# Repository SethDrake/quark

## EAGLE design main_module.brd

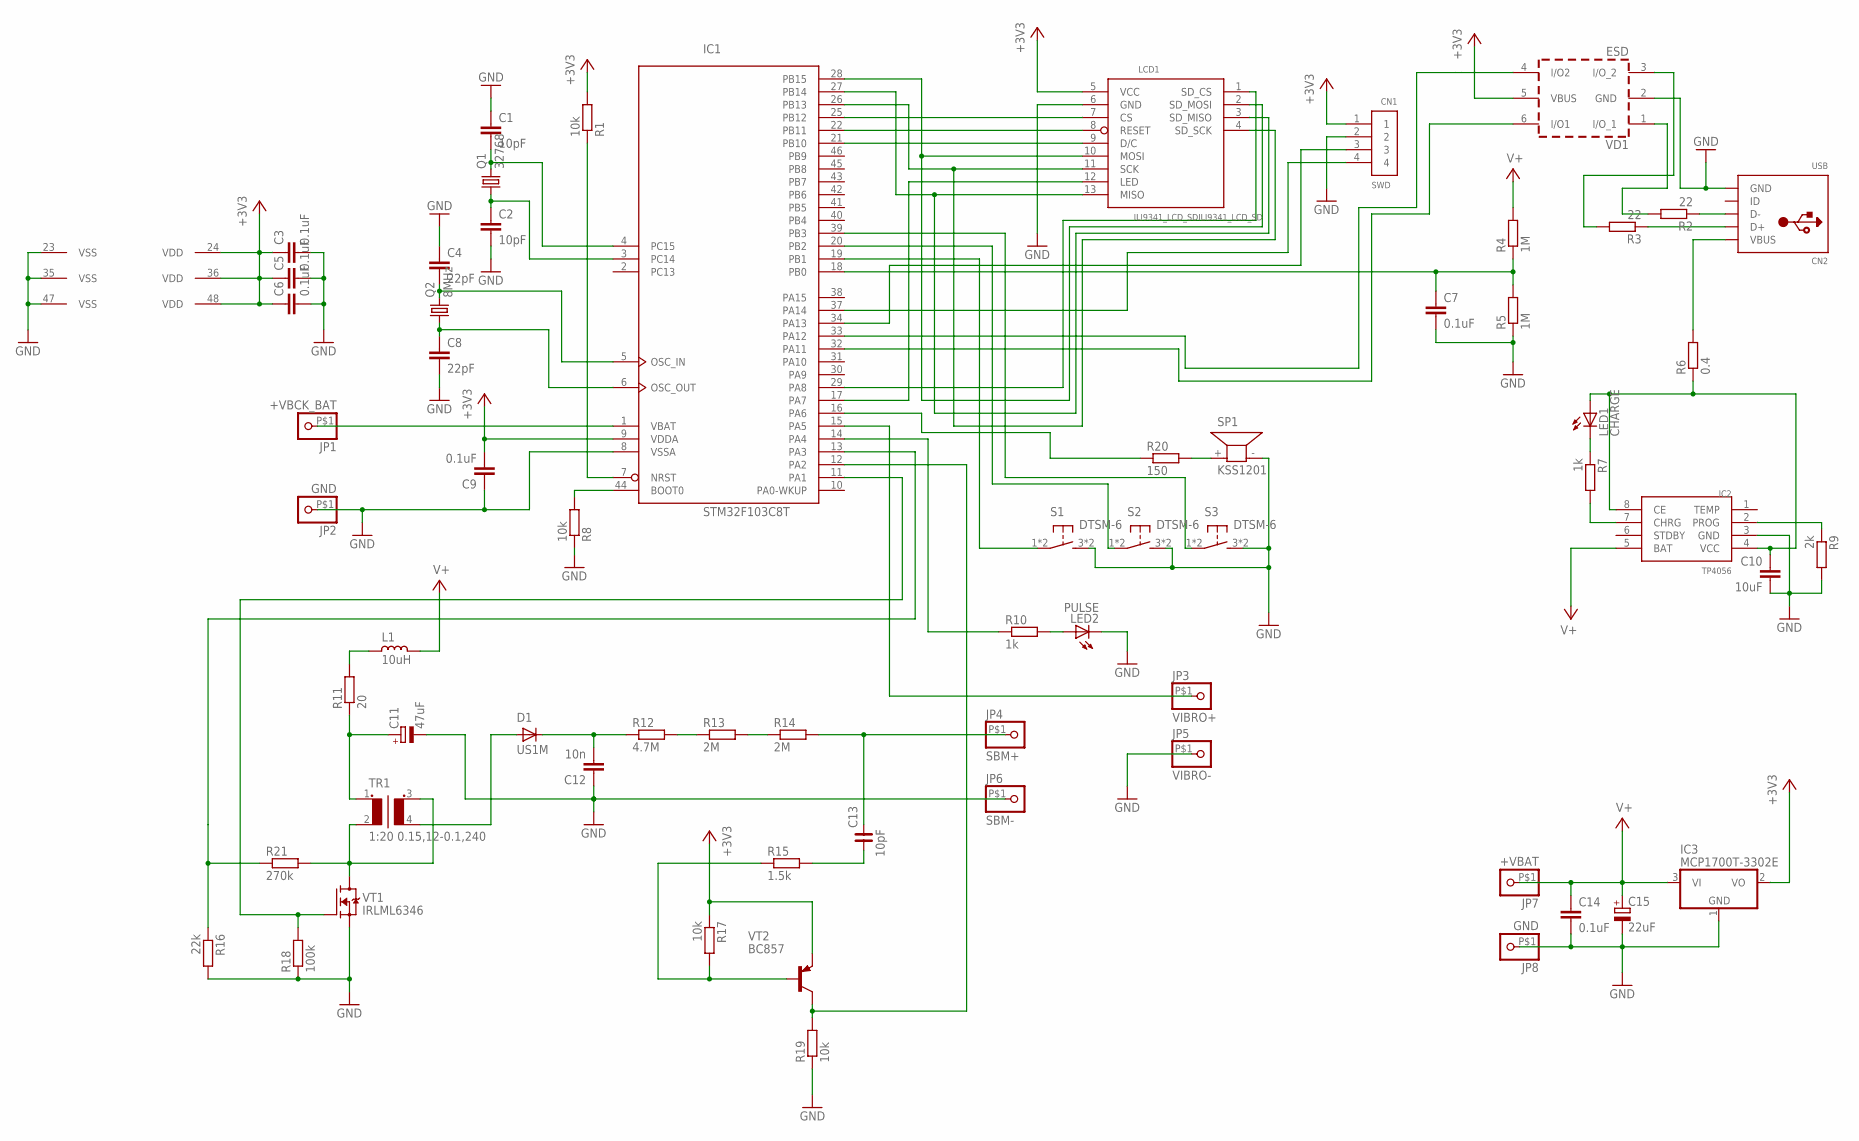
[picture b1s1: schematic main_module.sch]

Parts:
C1, C2: 10pF; C0805
C3, C5, C6, C7, C9, C14: 0.1uF; C0805
C4, C8: 22pF; C0805
C10: 10uF; C0805
C11: 47uF; C/6032-28R
C12: 10n; C1206
C13: 10pF; C1206
C15: 22uF; C/6032-28R
CN1: SWD; 1X04-BIG
CN2: USB; USB-MINIB
D1: US1M; SMA-DO214AC
IC1: STM32F103C8T; LQFP48
IC2: TP4056; SOP-8
IC3: MCP1700T-3302E; SOT23
JP1: +VBCK_BAT; 1X1-BIGPOGO
JP2, JP8: GND; 1X1-BIGPOGO
JP3: VIBRO+; 1X1-BIGPOGO
JP4: SBM+; 1X1-BIGPOGO
JP5: VIBRO-; 1X1-BIGPOGO
JP6: SBM-; 1X1-BIGPOGO
JP7: +VBAT; 1X1-BIGPOGO
L1: 10uH; L0805
LCD1: ILI9341_LCD_SDILI9341_LCD_SD; ILI9341_LCD_SD
LED1: CHARGE; CHIP-LED0805
LED2: PULSE; LED3MM
Q1: 32768; HC49/S
Q2: 8MHz; HC49/S
R1, R8, R17, R19: 10k; M0805
R2, R3: 22; M0805
R4, R5: 1M; M0805
R6: 0.4; M1206
R7, R10: 1k; M0805
R9: 2k; M0805
R11: 20; M0805
R12: 4.7M; M0805
R13, R14: 2M; M0805
R15: 1.5k; M0805
R16: 22k; M0805
R18: 100k; M0805
R20: 150; M0805
R21: 270k; M0805
S1, S2, S3: DTSM-6
SP1: KSS1201
TR1: 1:20 0.15,12-0.1,240; RING-TRANS
VD1: ESD; SOT-23-6L
VT1: IRLML6346; SOT23
VT2: BC857; SOT23-BCE

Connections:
32OSC_IN: C1.2, IC1.4 (PC15), Q1.2
32OSC_OUT: C2.1, IC1.3 (PC14), Q1.1
+3V3: C3.1, C5.1, C6.1, C9.2, CN1.1, IC1.9 (VDDA), IC1.24 (VDD), IC1.36 (VDD), IC1.48 (VDD), IC3.2 (VO), LCD1.5 (VCC), R1.2, R17.1, VD1.5 (VBUS), VT2.E
+VBCK_BAT: IC1.1 (VBAT), JP1.P$1
BATT_CTRL: C7.1, IC1.18 (PB0), R4.1, R5.2
GND: C1.1, C2.2, C3.2, C4.1, C5.2, C6.2, C7.2, C8.2, C9.1, C10.2, C11.-, C12.1, C14.2, C15.-, CN1.2, CN2.GND, IC1.8 (VSSA), IC1.23 (VSS), IC1.35 (VSS), IC1.47 (VSS), IC2.3 (GND), IC3.1 (GND), JP2.P$1, JP5.P$1, JP6.P$1, JP8.P$1, LCD1.6 (GND), LED2.K (C), R5.1, R8.1, R9.2, R16.2, R18.1, R19.1, S1.3, S1.4 (3), S2.3, S2.4 (3), S3.3, S3.4 (3), SP1.- (2), VD1.2 (GND), VT1.2 (S)
HV_OUT: C12.2, D1.K (C), R12.1
HV_PULSE: IC1.12 (PA2), R19.2, VT2.C
HV_PUMP: IC1.11 (PA1), R18.2, VT1.1 (G)
HV_TEST: IC1.13 (PA3), R16.1, R21.1
HV_TR_OUT: D1.A, TR1.4 (S2)
KEY1: IC1.19 (PB1), S1.1, S1.2 (1)
KEY2: IC1.20 (PB2), S2.1, S2.2 (1)
KEY3: IC1.39 (PB3), S3.1, S3.2 (1)
LCD_BACKLIGHT: IC1.17 (PA7), LCD1.12 (LED)
LCD_CS: IC1.25 (PB12), LCD1.7 (CS)
LCD_RESET: IC1.22 (PB11), LCD1.8 (RESET)
LCD_RS: IC1.21 (PB10), LCD1.9 (D/C)
LED_PULSE: IC1.14 (PA4), R10.1
MISO: IC1.27 (PB14), LCD1.3 (SD_MISO), LCD1.13 (MISO)
MOSI: IC1.28 (PB15), LCD1.2 (SD_MOSI), LCD1.10 (MOSI)
unnamed: R13.2, R14.1
unnamed: R20.2, SP1.+ (1)
unnamed: R12.2, R13.1
unnamed: IC1.7 (NRST), R1.1
unnamed: L1.2, R11.2
unnamed: C13.1, R15.2
unnamed: C10.1, IC2.4 (VCC), IC2.8 (CE), LED1.A, R6.1
unnamed: LED2.A, R10.2
unnamed: R15.1, R17.2, VT2.B
unnamed: C11.+, R11.1, TR1.1
unnamed: IC1.44 (BOOT0), R8.2
unnamed: CN2.D-, R2.1
unnamed: CN2.D+, R3.1
unnamed: IC2.2 (PROG), R9.1
unnamed: R21.2, TR1.2, TR1.3 (S1), VT1.3 (D)
unnamed: IC2.7 (CHRG), R7.2
unnamed: LED1.C, R7.1
OSC_IN: C4.2, IC1.5 (OSC_IN), Q2.2
OSC_OUT: C8.1, IC1.6 (OSC_OUT), Q2.1
SBM+: C13.2, JP4.P$1, R14.2
SCK: IC1.26 (PB13), LCD1.4 (SD_SCK), LCD1.11 (SCK)
SD_CS: IC1.29 (PA8), LCD1.1 (SD_CS)
SOUND: IC1.16 (PA6), R20.1
SWCLK: CN1.4, IC1.37 (PA14)
SWDIO: CN1.3, IC1.34 (PA13)
USB_DM: IC1.32 (PA11), VD1.6 (I/O1)
USB_DM_PROT: R2.2, VD1.1 (I/O_1)
USB_DP: IC1.33 (PA12), VD1.4 (I/O2)
USB_DP_PROT: R3.2, VD1.3 (I/O_2)
USB_POWER: CN2.VBUS, R6.2
V+: C14.1, C15.+, IC2.5 (BAT), IC3.3 (VI), JP7.P$1, L1.1, R4.2
VIBRO: IC1.15 (PA5), JP3.P$1

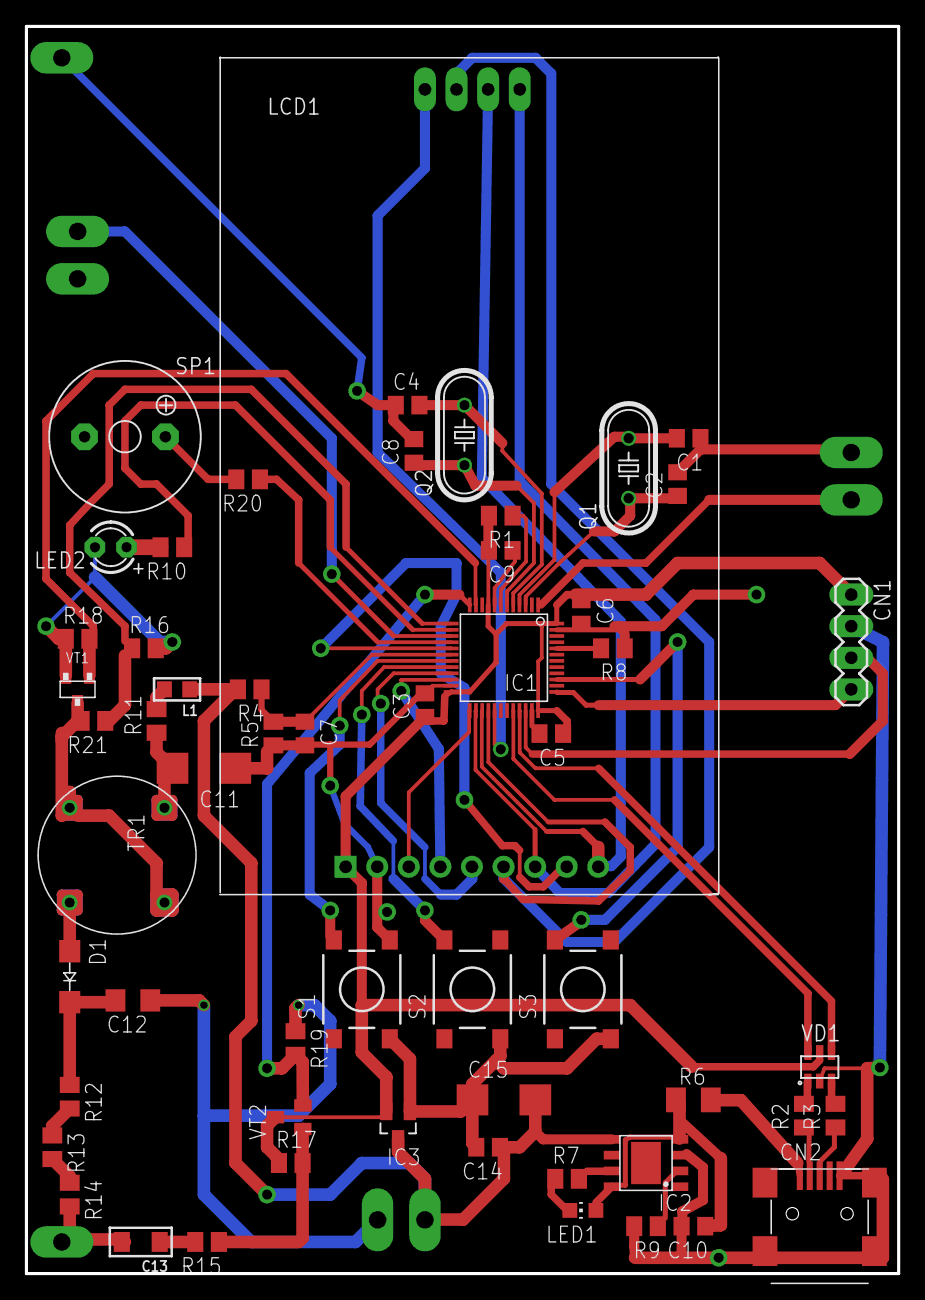
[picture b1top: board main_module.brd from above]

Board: 2 copper layers, 70.2 x 100.3 mm, 64 parts (0 on the bottom side), 53 nets.

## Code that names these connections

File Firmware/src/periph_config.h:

#pragma once
#ifndef __PERIPH_CONFIG_H_
#define __PERIPH_CONFIG_H_

/* PA13, PA14 - SWD - DON'T USE!!! */
/*        PA11, PA12 - USB		   */

#define HV_PUMP_PORT		GPIOA
#define HV_PUMP_PIN			GPIO_Pin_1
#define HV_PULSE_PIN		GPIO_Pin_2
#define HV_TEST_PIN			GPIO_Pin_3

#define INDICATION_PORT		GPIOA
#define IND_PULSE_PIN		GPIO_Pin_4
#define IND_VIBRATE_PIN		GPIO_Pin_5
#define IND_SOUND_PIN		GPIO_Pin_6

#define PWR_CONTROL_PORT	GPIOA
#define PWR_CONTROL_DISP	GPIO_Pin_7

#define SD_PORT				GPIOA
#define SD_PIN_CS			GPIO_Pin_8

#define BATT_CTRL_PORT		GPIOB
#define BATT_CTL_V_PIN		GPIO_Pin_0

#define KBRD_PORT			GPIOB
#define KEY_1_PIN			GPIO_Pin_1
#define KEY_2_PIN			GPIO_Pin_2
#define KEY_3_PIN			GPIO_Pin_3

#define ILI9341_PORT        GPIOB
#define ILI9341_PIN_RS      GPIO_Pin_10
#define ILI9341_PIN_RESET   GPIO_Pin_11
#define ILI9341_PIN_CS      GPIO_Pin_12

#define SPI_PORT			GPIOB
#define SPI_SCK				GPIO_Pin_13
#define SPI_MISO			GPIO_Pin_14
#define SPI_MOSI			GPIO_Pin_15

#endif //__PERIPH_CONFIG_H_

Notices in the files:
parts and their libraries:
rc-master-smd: Copyright (C) 2007, Bob Starr
